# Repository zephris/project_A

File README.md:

# PHBox

RP2350A arcade controller: 13/16-button layout, Kailh Choc V2 switches, per-key RGB, SH1106 OLED, USB-C input and top-side USB-A host port. Uses configurable GP2040-CE pin assignments; hardware compatibility remains a prototype test.

**30 October ergonomic revision:** [higher/wider PCB and matching case candidate](mechanical/ergonomic_layout_2026-10-30/README.md), with 32 mm action-column spacing, 20 mm Choc V2-compatible SGF MonKeys/generic round caps and more palm space. The cap selection and cover-opening inputs are updated; current export status is recorded in the candidate README. Electrical routing remains unfinished. The root PCB and earlier mock-print packages retain the preceding layout.

The **[replacement-only A1 print job](mechanical/ergonomic_layout_2026-10-30/REPRINT_A1/README.md)** regenerates the changed mock parts plus three PLA blanking plugs as one supported vertical stack. It uses PLA models and PETG release interfaces; unchanged pieces of the earlier kit are reused.

## Active design and manufacture

- Active KiCad 10 sources: [project](Flatbox-rev8.kicad_pro), [schematic](Flatbox-rev8.kicad_sch), [PCB](Flatbox-rev8.kicad_pcb), plus local libraries and `3dmodels`.
- **USB2 moved to the top on 8 October:** [revision and checks](mechanical/USB2-top-assessment-2026-10-08.md). Existing manufacturing files below are the preceding bottom-side revision; regenerate Gerbers/CPL and visually approve USB2 orientation before ordering the current PCB.
- [Manufacturing package](manufacturing/PHBox_2026-10-06_DFM_resolved/README.md), [complete ZIP](manufacturing/PHBox_2026-10-06_DFM_resolved.zip), [mandatory notes](manufacturing/PHBox_2026-10-06_DFM_resolved/MANUFACTURING-NOTES.md) and [DFM evidence](manufacturing/PHBox_2026-10-06_DFM_resolved/validation/rerun-summary.md).
- C41 / C29936 is included in BOM/CPL. Refresh the separate BOM matching site and visually approve placements, especially USB2, before assembly release.
- **USB2 replaced on 9 October:** [C2344 through-hole revision and checks](mechanical/USB2-C2344-assessment-2026-10-09.md). Uses Jing 902-131A1021D10100, with a drawing-derived STEP seated at the PCB datum. Existing manufacturing exports and quote still need regeneration; request mixed-assembly solder-process review for this through-hole part.

## Ordering guide

Current quote selections read on 8 October 2026; no order submitted. These are selected form values, not factory acceptance.

| Option | Selected value |
|---|---|
| Base material / material grade | FR-4 / FR4 TG135 |
| Layers / product type | 4 / Industrial/Consumer electronics |
| Designs / delivery | 1 / Single PCB |
| PCB quantity | 5 |
| Thickness | 1.6 mm |
| Mask / silkscreen | Black / White |
| Surface finish | HASL (with lead) |
| Outer / inner copper | 1 oz / 0.5 oz |
| Specify layer sequence / stackup | Yes / Yes |
| Stackup | JLC04161H-7628 |
| Impedance control | No requirement |
| Via covering | Epoxy Filled & Capped (selected; control currently disabled) |
| Via plating | Horizontal Electroless Copper Plating |
| Minimum via hole/land | 0.3 mm / 0.4–0.45 mm |
| Outline tolerance | ±0.2 mm (Regular) |
| Confirm production files | Yes; automatic approval disabled in earlier verified dialog |
| Mark / electrical test | Remove Mark / Flying Probe Fully Test |
| Gold fingers / castellated holes | No / No |
| Press-fit holes / edge plating | No / No |
| Blind slots / backdrill | No / No |
| UL marking / humidity indicator card | No / No |
| PCBA type / assembly side | Standard / Both Sides |
| PCBA quantity | 5 |
| Edge rails/fiducials | Added by JLCPCB; two 5 mm rails |
| Confirm parts placement | Yes |
| Stencil storage / fixture storage | No / No |
| Parts selection | By Customer (Self-Service) |
| Separate stencil order | Not enabled; no separate stencil thickness selected |

The quote displays **272.6 × 181 mm including assembly rails**; finished board artwork is **272.65 × 171.05 mm**. Follow the Gerber outline and verify dimensions in production artwork; do not resize the PCB to the rail-inclusive size. A depaneling service is suggested by the page but its selection is not verified.

Upload the [Gerber-only ZIP](manufacturing/PHBox_2026-10-06_DFM_resolved/upload/PHBox-DFM-resolved-Gerbers.zip), then [BOM](manufacturing/PHBox_2026-10-06_DFM_resolved/assembly/BOM-JLCPCB.csv) and [CPL](manufacturing/PHBox_2026-10-06_DFM_resolved/assembly/CPL-JLCDFM.csv) separately. Refresh the separate BOM matching site and visual preview, including C41 and USB2.

### Additional requirements and remarks

The **PCB remark is currently empty** in the live form, despite earlier entry; re-enter before submission. The current page does not expose a PCBA remark field. The short text below is prepared for that field, not already entered.

- Obtain explicit CAM confirmation that all nine **U1 0.35 mm ComponentDrill thermal holes** receive epoxy filling and copper capping. Ordinary via selection alone is insufficient. Preserve other component holes and use the supplied U1 hole map.
- Preserve U4's six **0.664 × 0.190 mm** paste apertures; obtain complete-board approval of a **0.10 mm stencil**. These are additional instructions, not selected quote options. Confirm X-ray inspection of U1's hidden exposed-pad joint.
- Confirm hand/THT assembly, OLED support and socket procurement. Retain manufacturer-land-pattern dispositions for D21/U1/U4/F1; verify polarity and accepted CPL rotations.
- **Leaded HASL differs from the source's Lead-Free setting.** Resolve finish before submission. Impedance control is not selected; USB impedance remains an engineering check against the chosen stackup.

Short additional-order remark (181 characters):

> U1: fill/cap 9 thermal ComponentDrill holes; X-ray EP joint. U4: keep 6 paste apertures 0.664x0.190mm; review 0.10mm stencil. Confirm manual parts, polarity and CPL before assembly.

The complete [manufacturing notes](manufacturing/PHBox_2026-10-06_DFM_resolved/MANUFACTURING-NOTES.md) and [ordering review](manufacturing/ordering-review-2026-10-08.md) retain dimensions, hole locations and acceptance requirements that cannot fit into one 200-character field.

## Final assembly by the user

Use the [sectioned final-assembly BOM and Perth-first supplier list](mechanical/assembly_bom_2026-10-31/README.md)
for quantities, purchasing status and exact-size requirements. It covers one unit
with 16 Choc V2 switches, 13 fitted 20 mm caps and three PLA blanking plugs.
Custom PETG keycaps are an authorized fallback if exact purchased caps cannot be
obtained with practical delivery; no new keycap model is included in the BOM.

Use the [current wider-layout part files](mechanical/ergonomic_layout_2026-10-30/README.md)
with the [17 mm sandwich assembly sequence](mechanical/sandwich_17mm_2026-10-08/README.md).
The wider PCB still requires routing and fresh manufacturing exports. Its combined
assembly STEP contains the earlier top cover; use the individual current parts.
This is a **prototype assembly guide**: nominal CAD fits have passed, but real
switches, hardware, foam and thermal pads must be trial-fitted before making the
finished enclosure. Overall case size is **292.6 × 191 × 17 mm**, excluding keycaps.

### How the parts are mounted

The layer order is **top acrylic → upper spacer and internal parts → PCB → foam
→ lower spacer/carrier → bottom acrylic**. The upper and lower spacer walls close
the perimeter; their heights are already included in the 17 mm total.

| Assembly | Mounting solution |
|---|---|
| Acrylic covers and spacer walls | Eight rigid columns outside the PCB: 12 mm M3 female/female spacers, with a 0.50 mm washer at each end. Screws enter from both covers. |
| PCB | Seven relieved foam pads beneath it; six upper foam pads capture the switch-plate tabs. Loose guides at H4/H6 locate it laterally. No case screws clamp through the PCB. |
| Choc V2 switch plate | Three custom insulating post/retainer pairs at H1/H2/H3, with polymer M3 screws. The 1.30 mm plate sits 3 mm above the PCB seating plane. |
| MCU/flash heatsink | Insulating hard stops, support washers and rear retainers at H5/H7/H12. Separate thermal pads contact U1 and U3. This attaches to the PCB, not the case. |
| OLED | Four custom insulating posts and rear caps, plus a corner frame and polymer M2 screws. The frame retains the module PCB without pressing its glass. |
| Option-button caps | Six captured plungers guided by the acrylic and a lower retainer. Two M2 screws secure the retainer to the cover; switch contact domes provide click and return. |
| USB ports | Integral spacer surrounds and compliant collars. Acrylic roofs USB-A; the spacer roofs USB-C. The collars close shell gaps while allowing PCB movement. |

The PCB, switch plate, heatsink and screen move together as one foam-supported
assembly. The CAD budgets ±0.50 mm XY and ±0.25 mm Z movement. Do not turn the
port collars, button guides or mounting screws into rigid links between it and
the outer case.

### Parts to prepare

| Part | Quantity / specification |
|---|---|
| Acrylic covers / printed spacer frames | One top and one bottom of each; acrylic is 2 mm thick |
| Case columns / end washers | 8 × M3 female/female, 12 mm, AF5; 16 × Ø7 / Ø3.4 / 0.50 mm washers |
| Case screws | 16 × M3×6, 90° countersunk |
| Switch-plate mounts / screws | 3 custom insulating post/cap pairs; 3 × M3×8 polymer, head no larger than Ø6 × 2.4 mm |
| OLED mounts / screws | 4 custom insulating post/cap pairs; 4 × M2×8 polymer, head no larger than Ø4 × 1.6 mm |
| Heatsink mounting set | 3 insulating hard stops, 3 support washers, 3 relieved rear washers and 3 tapped rear retainers; polymer M3 at H5/H7 and M2 at H12. Select screw lengths after measuring the assembled stack. |
| Thermal pads | Two electrically insulating pads: MCU 5.5 × 5.5 mm; flash 3.5 × 3.5 mm. Starting assumption: 0.50 mm free / 0.40 mm installed thickness. |
| Support foam | 7 lower pads from 2 mm stock; 6 upper pads from 1.5 mm stock, using the supplied cut profiles |
| Port collars | 2 printed unfilled, nonconductive TPU 95A trial collars, 2 mm deep; separate front-face-down STLs include the rear PCB rebates |
| Option caps / retainer / fasteners | 6 caps, 1 retainer, 2 × M2×5 pan-head screws (head ≤ Ø4 × 1.6 mm), 2 × M2 nuts (AF4 × 1.6 mm) |

Custom insulating mounts and retainers are supplied CAD parts, not ordinary
catalog standoffs. The heatsink uses flat insulating support washers in the
current model; an O-ring is an alternative only after checking its compressed
height and force. Keep the hard stops with either choice. Exact foam and thermal-pad
grades, heatsink screw lengths and the option-switch MPN remain to be qualified.

### TPU USB collars

Print one each of [USB-A](mechanical/sandwich_17mm_2026-10-08/STL/usb_a_collar.stl) and
[USB-C](mechanical/sandwich_17mm_2026-10-08/STL/usb_c_collar.stl). Both files are oriented
front mating face down on Z=0, with the rear PCB relief upward. Use unfilled,
nonconductive TPU 95A as the economical first trial. The PCB supports remain cut
foam and the other mounts keep their existing materials.

Start with 0.10 mm layers, dried filament and the filament maker's temperature
profile. Inspect the sliced rear relief: it leaves a **0.317 mm front membrane**.
Check that it prints continuously without tears; do not thicken it into the PCB
clearance. The supplied orientation avoids a roof over the rear relief. Trial
both collars before printing the full case, checking insertion, unplugging,
retention and freedom of the foam-mounted PCB. The intentional interference is
0.20 mm at the outer surround and 0.10 mm at the nominal connector shell.

Saved geometry clears the PCB travel envelope; TPU stiffness, creep and retention
have not been physically qualified. The collars close gaps but have no ingress
rating. Ordinary TPU does not replace the electrically insulating thermal pads.
[Prusa flexible-filament guidance](https://help.prusa3d.com/article/flexible-materials_2057)
explains printing and drying considerations.

### Buying materials: cost and delivery priority

For an unpowered fit trial, use the [printed mock-kit guide](mechanical/sandwich_17mm_2026-10-08/MOCK_ONLY/README.md): individual STLs include acrylic surrogates, case columns, mounting parts, collars and simplified PCB/display envelopes. Large parts have quarter-panel alternatives. Plastic heatsink and rigid pad gauges are for geometry checks only; do not power the board with them fitted.

The **[35-step illustrated mock assembly manual](mechanical/sandwich_17mm_2026-10-08/MOCK_ONLY/output/pdf/PHBox_mock_assembly_manual.pdf)** shows one operation per page, quantities, movement arrows, underside details and fit checks. Its [linked text version](mechanical/sandwich_17mm_2026-10-08/MOCK_ONLY/ASSEMBLY_STEPS.md) identifies every STL file used.

The [Bambu A1 PLA print package](mechanical/sandwich_17mm_2026-10-08/MOCK_ONLY/PRINT_A1/README.md) contains one part per 3MF project and validated slice for 0.6/0.4/0.2 mm nozzles. Six oversized parts are split into four sections each. The required kit has 86 individual files, about 471 g / 26.6 hours when printed separately; 19 optional gauge/envelope files are also supplied. Use one AMS Lite PLA colour per print; these estimates exclude nozzle changes, handling and physical fit qualification.

For the requested **single vertically stacked job**, use the [A1 PLA/PETG stack guide](mechanical/sandwich_17mm_2026-10-08/MOCK_ONLY/STACK_A1/README.md). All 105 parts retain their geometry inside an editable multipart assembly. Independently rising panel columns and low side pockets reduce support; 1 mm supported separators use PETG on both contact faces and PLA scaffold inside. The guide includes the small separation trial, full project/slice, actual estimates, numbered views and assembly-review limitations. Print the trial before the full stack.

The [31 October assembly BOM](mechanical/assembly_bom_2026-10-31/README.md)
supersedes the older AliExpress-first sourcing preference. Prioritise **Perth
pickup**, then Australian shipped exact parts, and international suppliers where
no exact local match is verified. It lists local thermal pads, hardware inquiries,
foam, acrylic cutting and aluminium machining. Exact store stock, fastener head
dimensions and custom quotes still need confirmation where marked. No purchases
or supplier inquiries have been made. The older
[materials list](mechanical/sandwich_17mm_2026-10-08/materials.md) remains a dated reference.

The [heatsink hardware audit and mounting alternatives](mechanical/sandwich_17mm_2026-10-08/heatsink-hardware-options.md)
lists concrete nylon screw/nut and case-column sources. Current heatsink rear
retainers provide only 2 mm nominal thread depth; screw length and engagement
remain unresolved. A PETG shoulder stop with stock nylon nuts in redesigned
capture carriers is the preferred prototype direction, subject to fit and
thermal/preload trials. TPU should not replace the height-setting hard stops.

### Assembly sequence

**Read the graphic from I upward:** build the lower case (I/H), add support foam (G), lower the assembled PCB and its attachments (F/E/D), then add the upper foam, spacer and prepared cover (C/B/A). Letters identify parts; the numbered steps below give the working sequence. Exploded gaps are illustrative, not installed heights.

The sections explain which parts clamp together and which must remain free to move. They are not machining drawings; use the hardware table and supplied STEP parts for dimensions. Full-resolution images are available by opening each graphic.

1. **Prepare and dry-fit the parts.** Deburr acrylic and aluminium, clean the
   printed guides and trial a real Choc V2 switch in the plate coupon. Check the
   actual PCB thickness, OLED tails, fastener heads and option-switch height.
   Acrylic case holes require the specified secondary 90° countersinks; support
   them during machining and trial a coupon before cutting the full covers.
2. **Build the PCB assembly.** Fit the OLED posts, module, corner frame and rear
   caps using the four polymer M2 screws. Attach the switch plate at H1/H2/H3
   using its three insulating mounts and polymer M3 screws. Fit the switches and
   confirm latching. Keep screw and frame loads off the OLED glass.
3. **Fit the heatsink.** Measure U1/U3 package heights and select the thermal-pad
   grade before setting contact gaps. Centre the two small pads on the package
   bodies, clear of leads and nearby components. Fit the insulating stops,
   washers and rear retainers at H5/H7/H12. Tighten only to the hard stops;
   inspect pad compression and PCB bending. BOOTSEL/RESET remain clear of the
   aluminium and are serviced by removing the top cover.
4. **Build the lower case.** Fit the eight columns, lower end washers and lower
   frame to the bottom acrylic with eight case screws. Place the seven lower
   foam pads in their relieved seats. Keep foam off sockets, solder tails and
   rear components. Lower the PCB assembly over the loose H4/H6 guides.
5. **Prepare the top cover.** Insert the six option caps from below, with their
   retaining flanges beneath the acrylic. Fit the lower retainer, captive nuts
   and two M2×5 screws. Check that each cap slides freely. No extra coil springs
   are required in this candidate.
6. **Fit the surrounds and close the case.** Place the six upper foam pads on
   the switch-plate capture tabs. Fit the upper spacer and the two port collars,
   including their printed rear PCB rebates. Trial the outer interference fit;
   if collars walk out, qualify thin TPU-compatible perimeter adhesive
   against their spacer seats; keep adhesive off the moving PCB and connector
   contacts. Add the upper end washers and top acrylic, then the remaining eight
   case screws. Tighten gently and evenly onto the fixed columns. Tune foam to
   achieve the PCB's rest height; do not pull the PCB down with case screw torque.
7. **Check mechanical operation before powering.** Every option cap must return
   and release its switch at both PCB travel extremes. Test full keycap stroke,
   screen retention and real USB cable/dongle insertion and removal. The USB-A
   fit gauge assumes a 2 mm setback between the mating face and dongle body;
   confirm this on the intended dongle. Check that the covers and foam do not
   contact rear tails or load the connector shells.
8. **Run the first-article checks.** Confirm all inputs, OLED, RGB and USB operation,
   then check MCU/flash temperatures in the closed case. Recheck cap return,
   foam rest height and fastener seating after initial use.

Use the [exploded STEP](mechanical/sandwich_17mm_2026-10-08/STEP/exploded.step)
to identify parts; its layer offsets are for presentation, not spacer dimensions.
The [detailed mechanical guide](mechanical/sandwich_17mm_2026-10-08/README.md)
contains cutting, countersink, clearance and fit-test specifications.

## Simulation and mechanics

- [17 mm foam sandwich mounting candidate](mechanical/sandwich_17mm_2026-10-08/README.md): acrylic covers, spacers/carrier, Choc V2 plate, screen frame/posts and integrated PCB/heatsink assembly. USB-A pocket ends at the main case edge, with a 2 mm acrylic USB-A roof, lower printed USB-C roof and integral soft-seal retaining lips at 17 mm overall; plan size 292.6 × 191 mm. Six captured option caps replace the exposed button slot. Fit candidate; actual switches, foam preload, seals and hardware tolerances need trials.
- [Mounting and Perth hardware sourcing](mechanical/mounting_sourcing_2026-10-08.md): gasket-supported PCB/heatsink/screen carrier, local fasteners and thermal-pad candidates; custom insulating stops remain necessary. [Choc V2 LED-window fit study](mechanical/choc_v2_led_fit_2026-10-08/README.md) contains fit/section STEP models and all-key clearance checks.
- [MCU/flash aluminium heatsink candidate](mechanical/heatsink_2026-10-08/README.md): milled plate, separate insulating thermal pads, BOOTSEL/RESET access and checked board fit. Contact heights and pad force still require assembled-hardware qualification.
- [SPICE suite](spice/README.md): 14 isolated benches; [latest results](spice/results_static_retest_2026-10-07.md). First articles still need power, USB suspend, firmware, thermal and dongle tests.
- [Enclosure principles](mechanical/enclosure_2026-10-05/DESIGN-PRINCIPLES.md), [candidates](mechanical/enclosure_2026-10-05/README.md), [PCB tolerances](mechanical/enclosure_2026-10-05/pcb_geometry/README.md) and [Z geometry](mechanical/enclosure_2026-10-05/z_geometry/index.html). Choc V1 plate references need V2 fit verification.
- USB2: Jing 902-131A1021D10100 / C2344, through-hole on the top side beside USB-C; [current assessment](mechanical/USB2-C2344-assessment-2026-10-09.md). The [sandwich candidate](mechanical/sandwich_17mm_2026-10-08/README.md) has a flat 17 mm case with an acrylic connector roof and open-top dongle pocket (2 mm dongle body setback requires a physical check); older 26 mm covers remain historical references. A 15 mm version needs further height changes.

`stage2_work` retains active parsers, production-silk generation and CAD dependencies; `kicad-happy-main` contains project skills. [Cleanup manifest](manufacturing/cleanup-manifest-2026-10-07.json).

The latest [reference-case study](mechanical/sandwich_17mm_2026-10-08/reference-case-study.md)
records the contoured USB surrounds, foam-motion clearances and option-button
comparison. USB-A is acrylic-roofed; USB-C is spacer-roofed. Captured H5 option
plungers rely on the tact switches for click/return, without auxiliary springs.

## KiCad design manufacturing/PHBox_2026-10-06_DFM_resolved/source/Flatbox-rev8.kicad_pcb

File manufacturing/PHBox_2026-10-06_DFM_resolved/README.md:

# Current PHBox demo fabrication and assembly package

The latest package includes C41 Samsung CL10B105KA8NNNC / C29936, 1uF/25V/X7R, at its existing bottom-side origin and zero rotation. BOM/CPL contain the same 112 designators in 36 BOM groups. Source metadata is updated; fabrication copper, drill, stencil and production silk files are unchanged. This metadata-only addition does not invalidate the saved PCB geometry review; refreshed online BOM matching/assembly preview remains required.

Use upload/PHBox-DFM-resolved-Gerbers.zip for PCB upload, assembly/BOM-JLCPCB.csv and assembly/CPL-JLCDFM.csv on the separate BOM matching page, and both stencil paste files with the assembler. The complete distributable is ../PHBox_2026-10-06_DFM_resolved.zip.

MANUFACTURING-NOTES.md is authoritative. The obsolete assembly-note.txt was removed. JLCPCB CAM must still confirm all nine U1 ComponentDrill thermal holes receive epoxy filling and copper capping. Obtain complete stencil approval, actual-package disposition and final production artwork review before ordering. Source silk is restored; use the supplied clearance-clipped production silk exports.

Saved final geometry analysis: validation/rerun-summary.md and findings-disposition.md. Website candidate 630408027919675394 predates adding C41 to assembly files. No online placement confirmation of C41 is claimed. Bare PCBA is an engineering prototype, with hardware/power/thermal qualification pending. Hot-swap sockets and mechanical support need an explicit assembly/procurement arrangement.

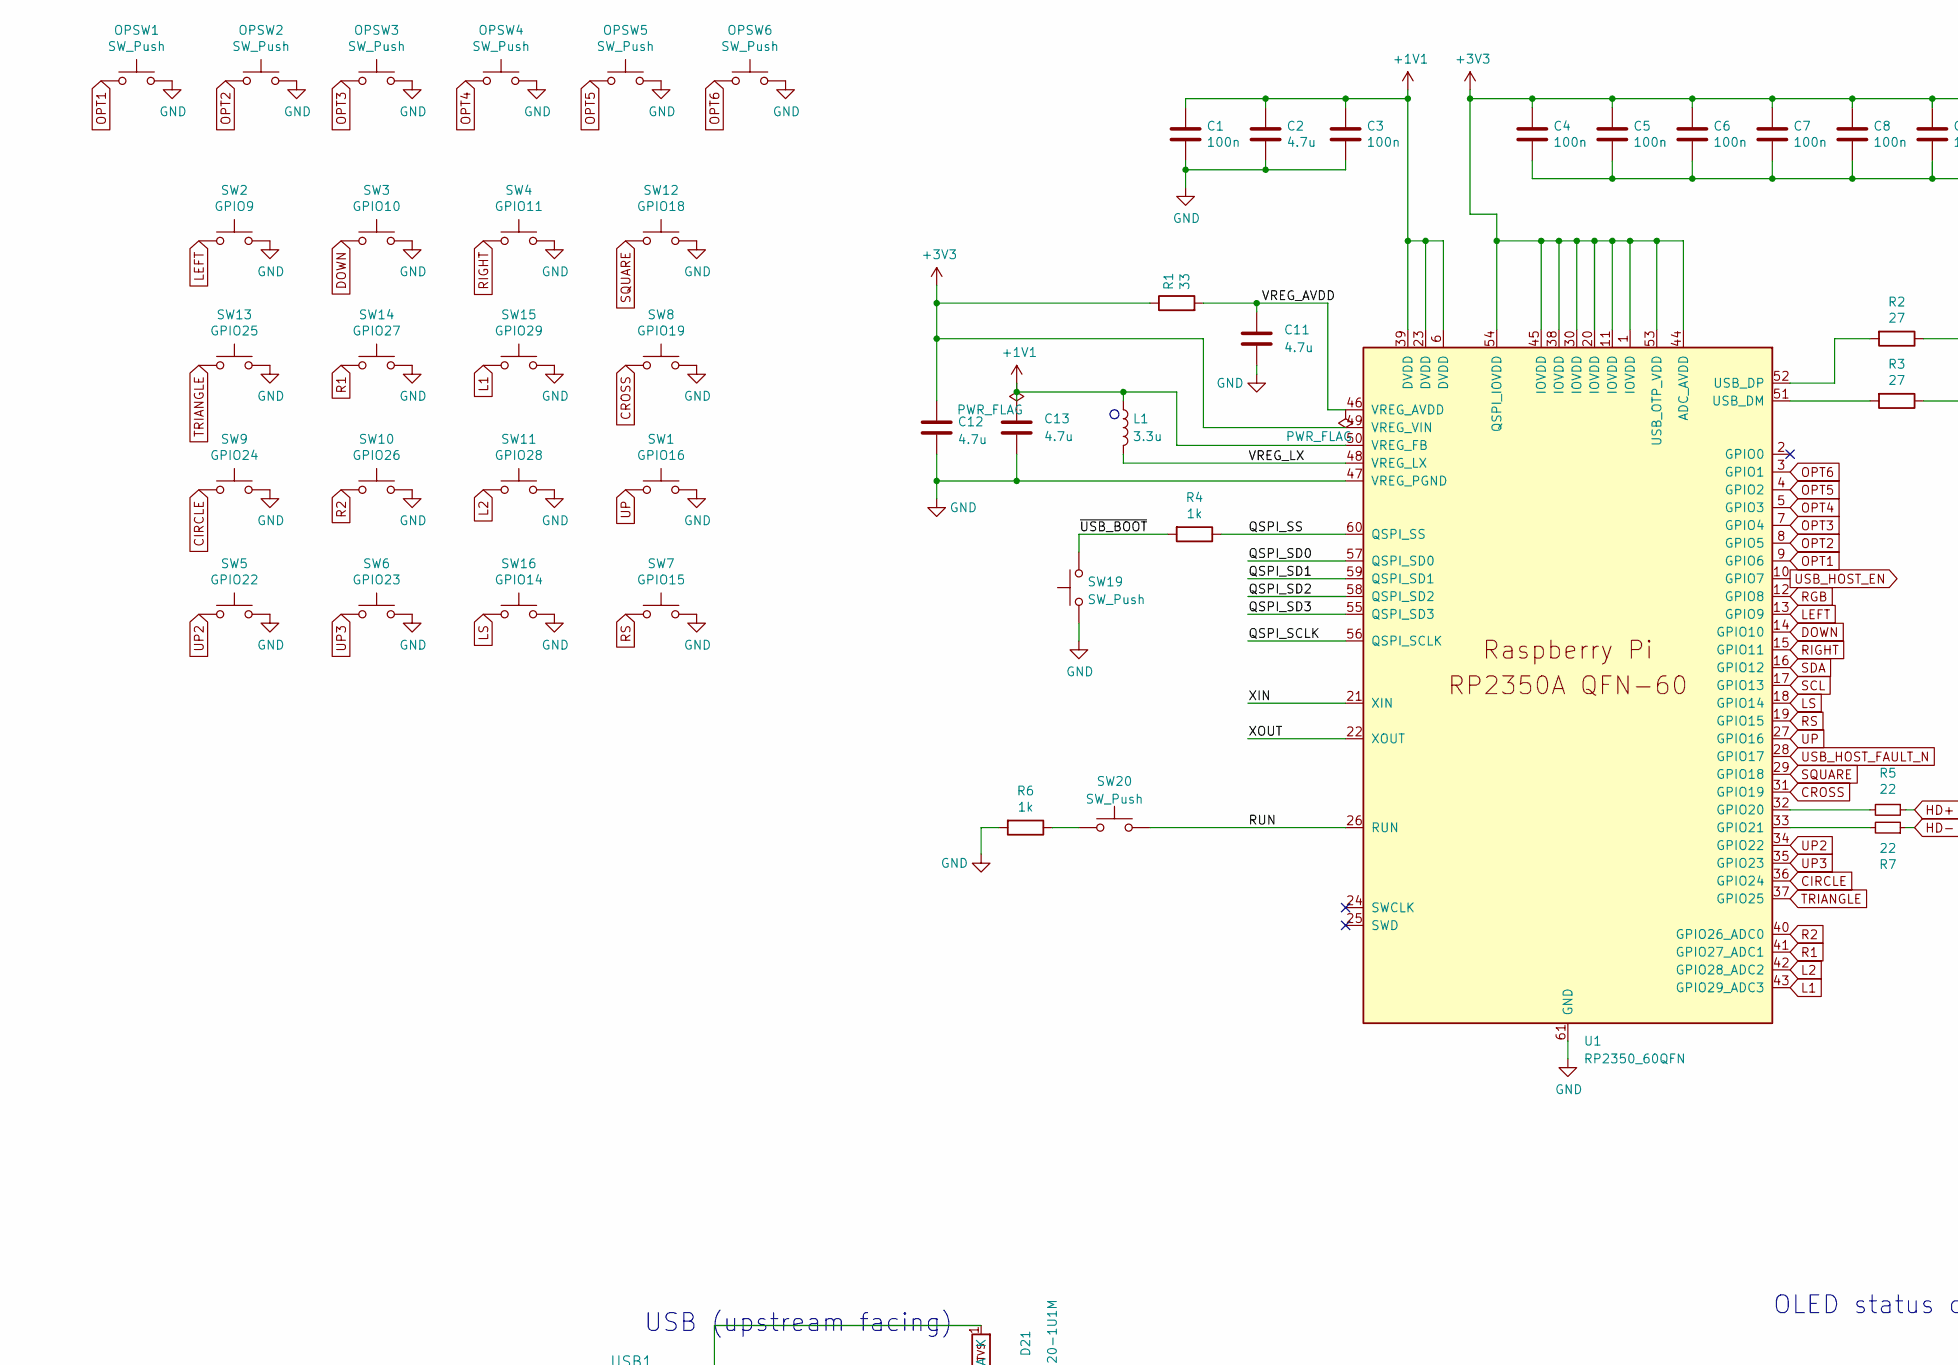
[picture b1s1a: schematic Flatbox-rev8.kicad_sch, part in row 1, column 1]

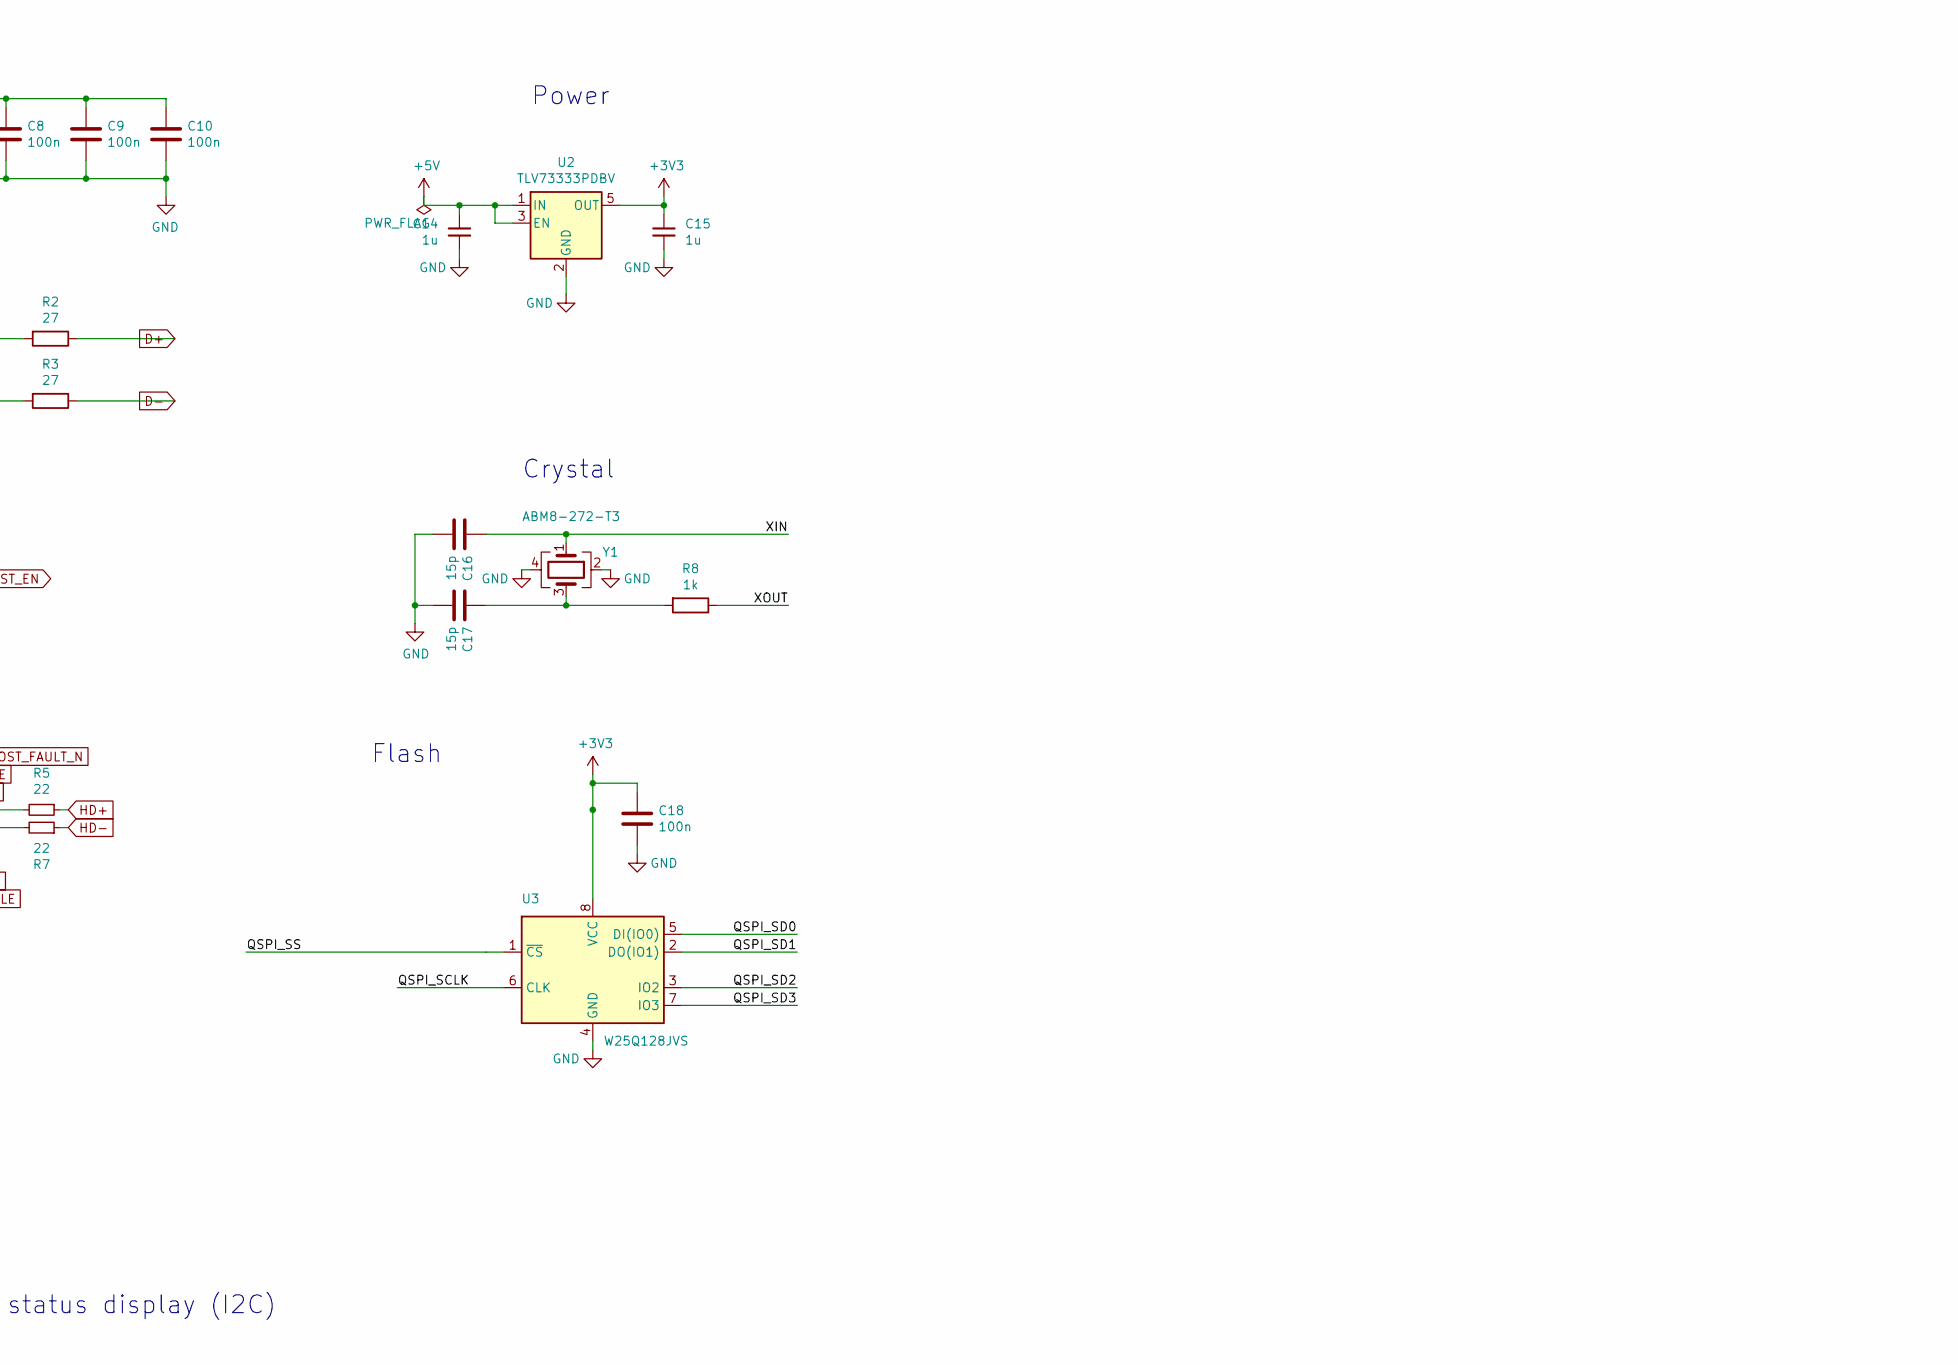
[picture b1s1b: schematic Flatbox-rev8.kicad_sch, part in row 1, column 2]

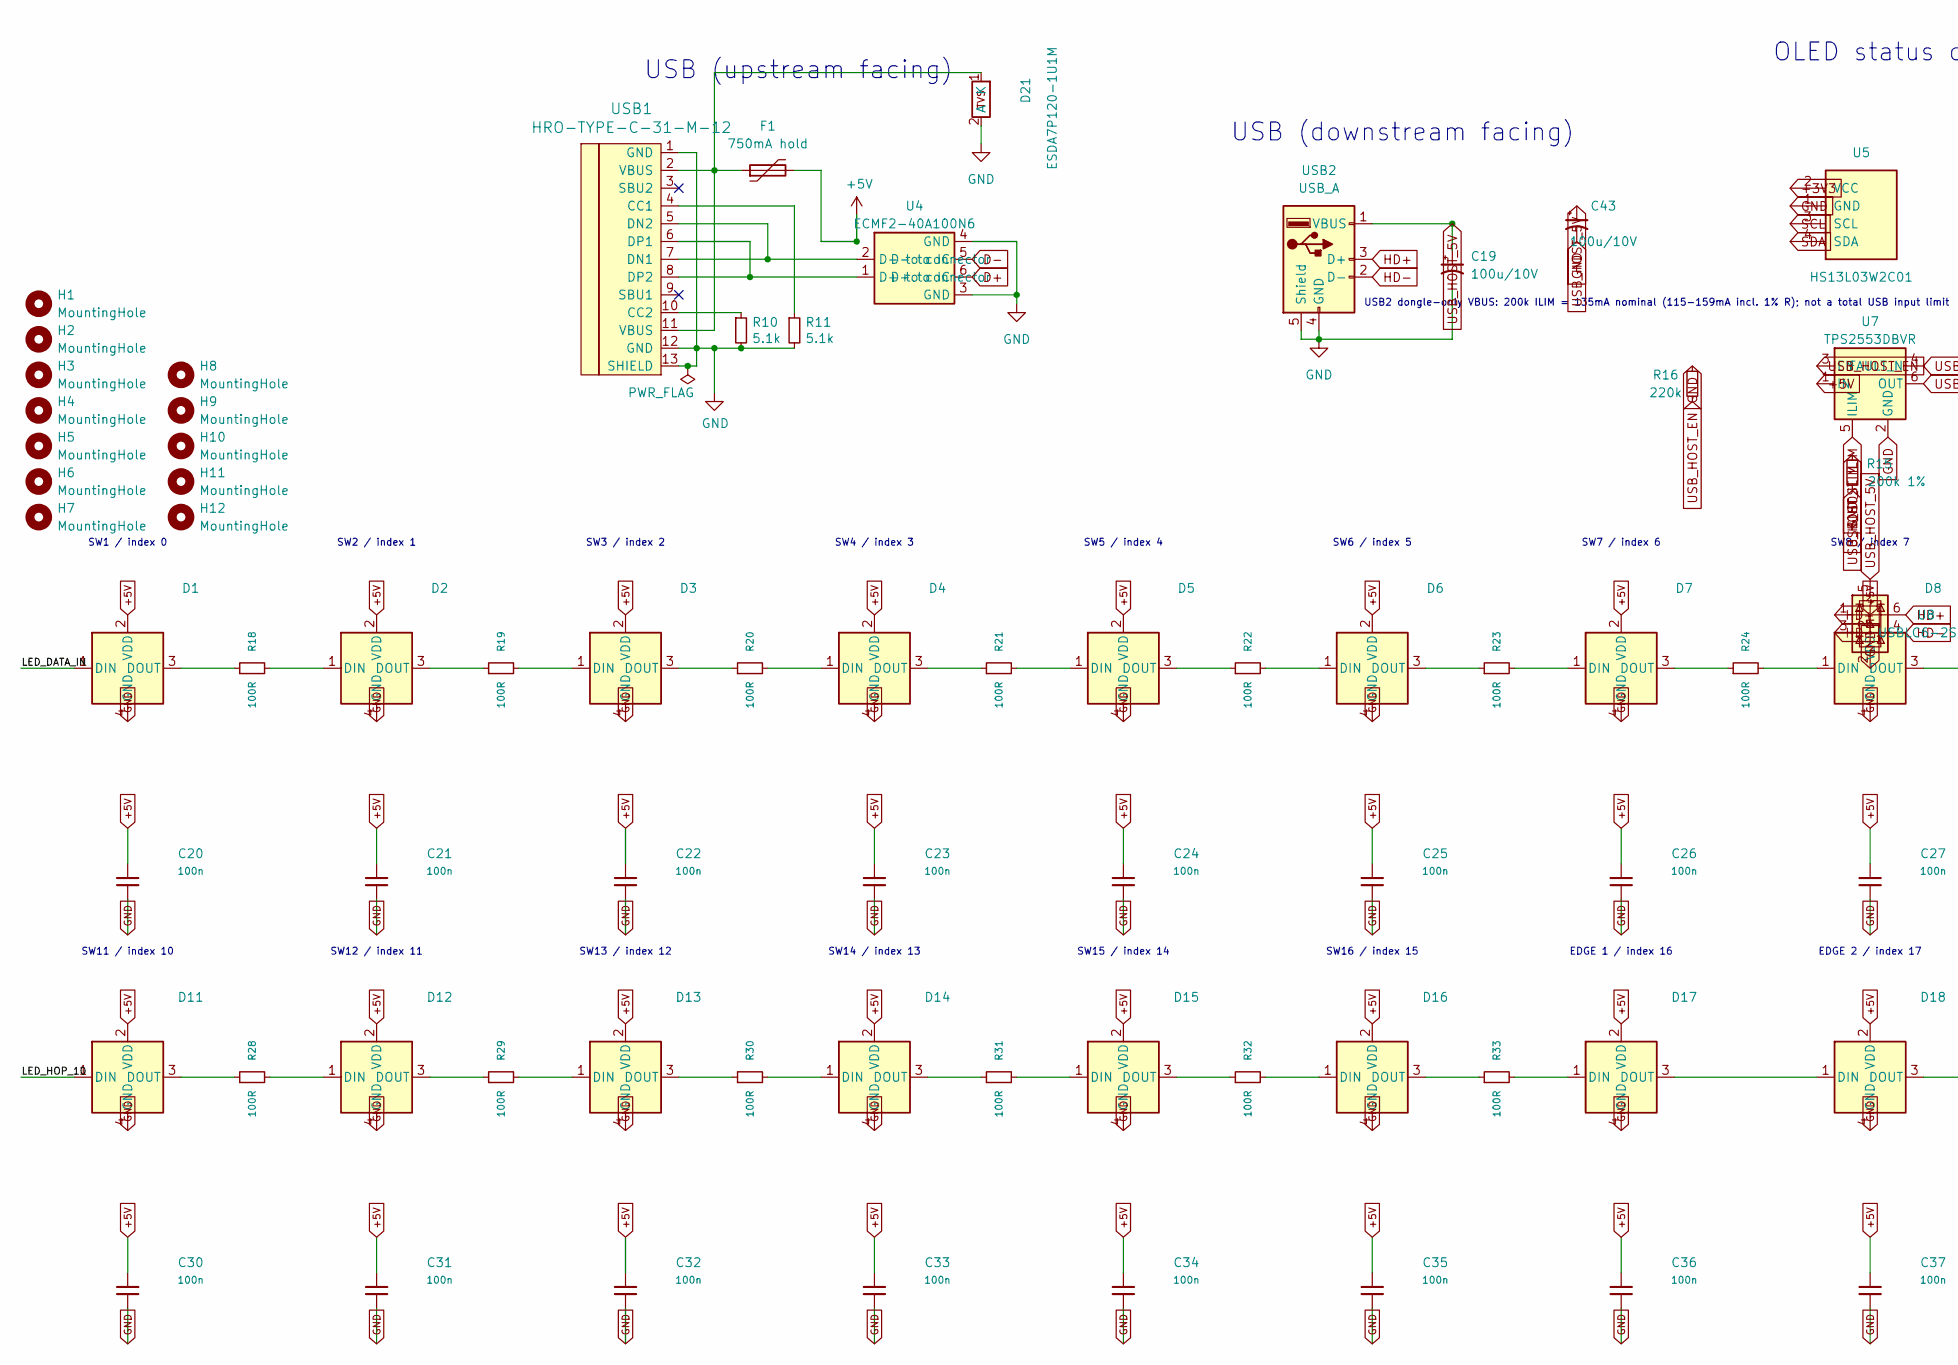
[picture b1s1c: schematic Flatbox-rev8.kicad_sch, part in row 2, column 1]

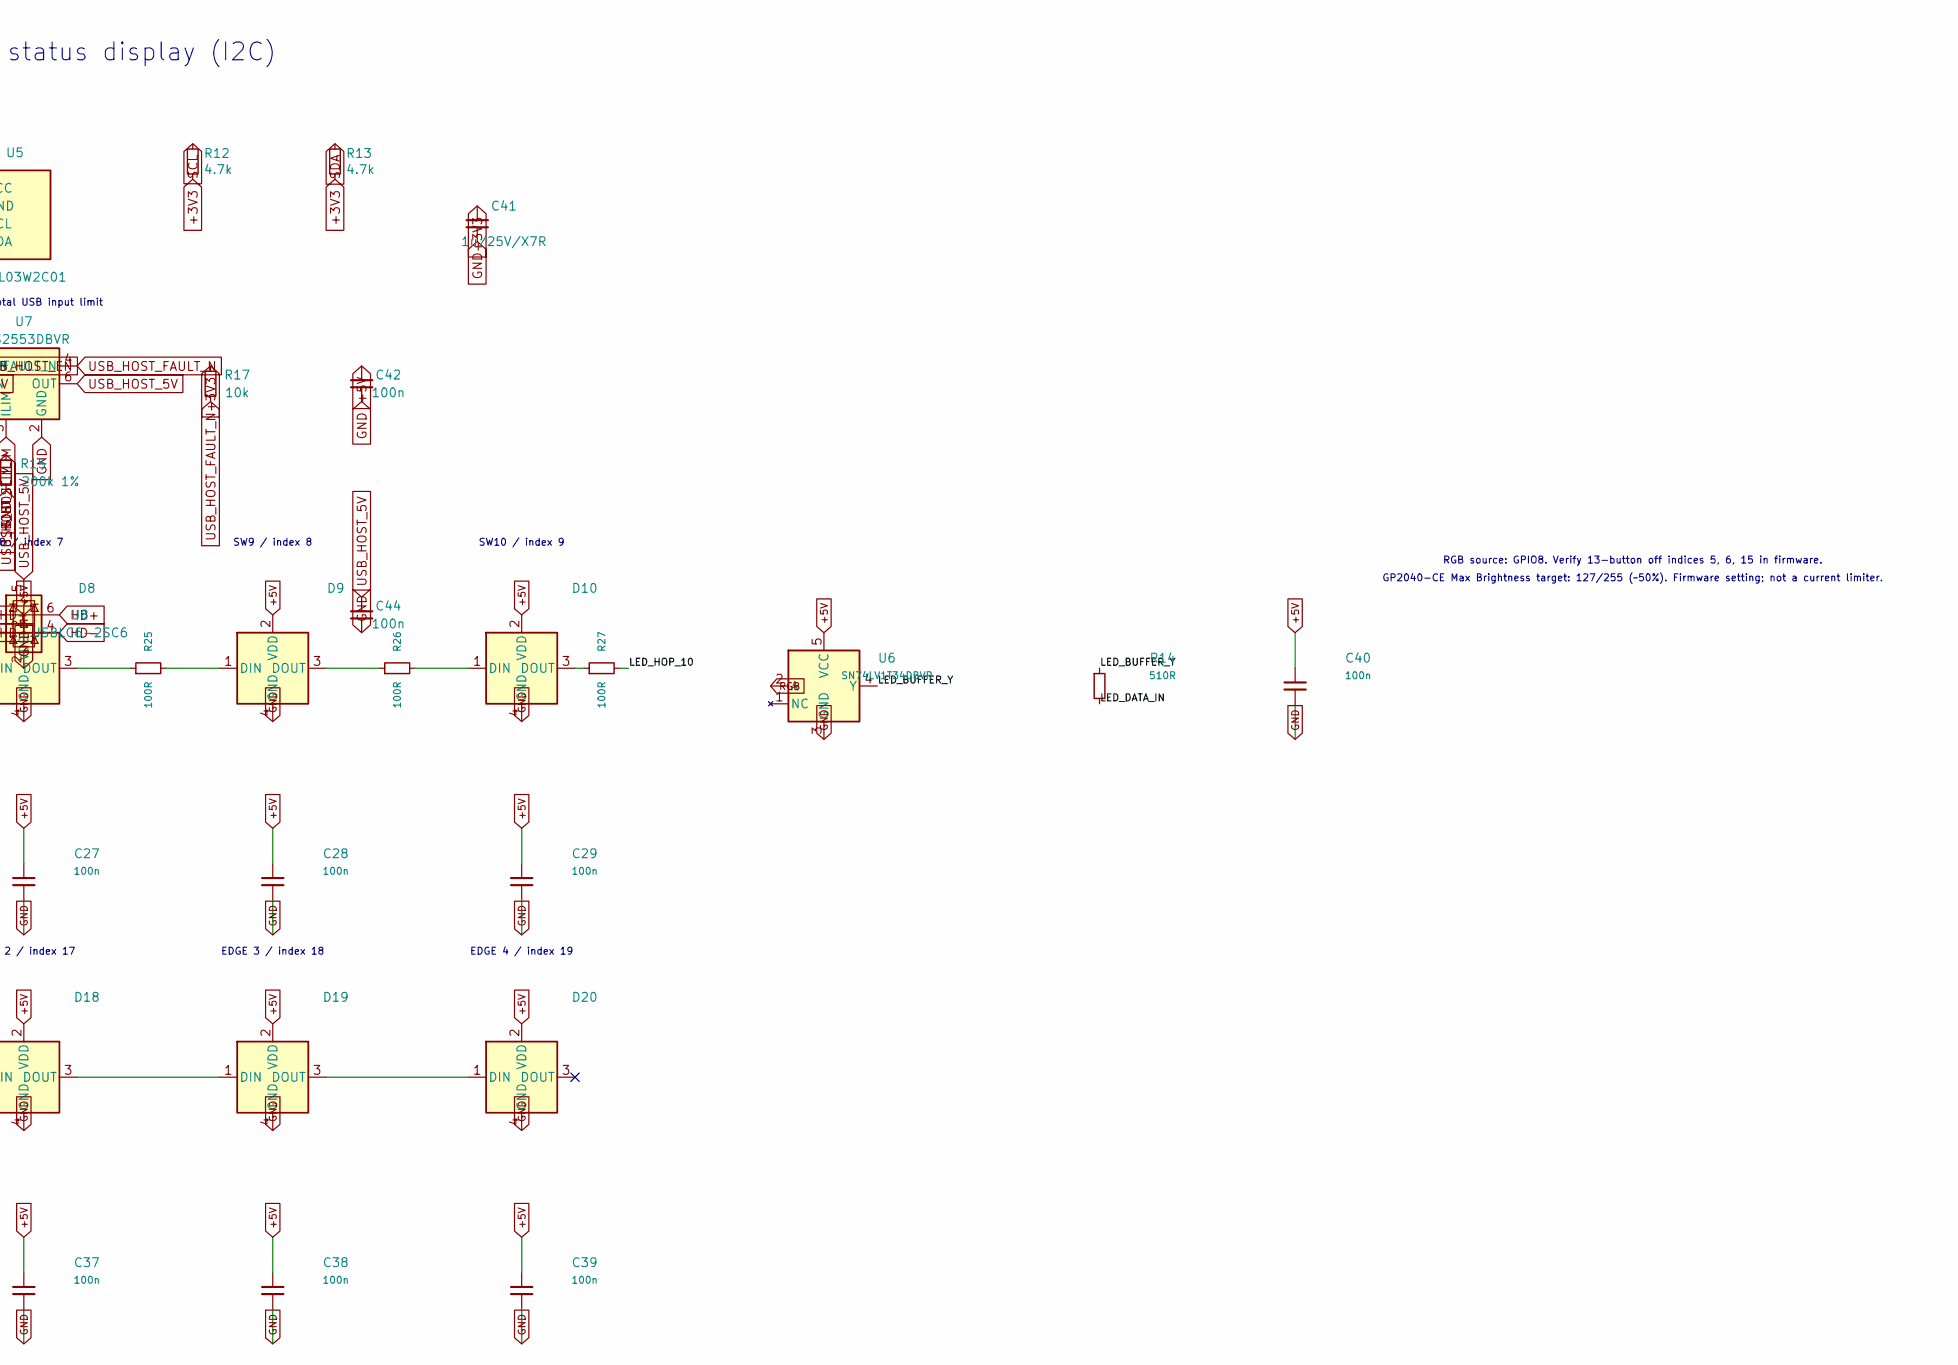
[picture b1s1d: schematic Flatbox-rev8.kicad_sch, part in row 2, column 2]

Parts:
C1, C3, C4, C5, C6, C7, C8, C9, C10, C18: 100n; C_0402_1005Metric; LCSC C1525
C2, C11: 4.7u; C_0402_1005Metric; LCSC C23733
C12, C13: 4.7u; Samsung_1005_Tolerance015; LCSC C23733
C14, C15: 1u; C_0402_1005Metric; LCSC C52923
C16, C17: 15p; C_0402_1005Metric; LCSC C1548
C19, C43: 100u/10V; CP_KEMET_T520B_3528_21; MPN T520B107M010ATE070; LCSC C600583
C20, C21, C22, C23, C24, C25, C26, C27, C28, C29, C30, C31, C32, C33, C34, C35, C36, C37, C38, C39, C40: 100n; Samsung_1005_Tolerance005; MPN CL05B104KO5NNNC; LCSC C1525
C41: 1u/25V/X7R; C_0603_1608Metric; MPN CL10B105KA8NNNC; LCSC C29936
C42, C44: 100n; C_0402_1005Metric; MPN CL05B104KO5NNNC; LCSC C1525
D1, D2, D3, D4, D5, D6, D7, D8, D9, D10, D11, D12, D13, D14, D15, D16, D17, D18, D19, D20: SK6805-EC15; LED_SK6805_EC15_Optical; MPN SK6805-EC15; LCSC C2890035
D21: ESDA7P120-1U1M; ESDA7P120_1U1M_ST_Recommended; MPN ESDA7P120-1U1M; LCSC C2969802
F1: 750mA hold; Fuse_TECHFUSE_SMD0805_075_12V; MPN SMD0805-075-12V; LCSC C19108399
H1, H2, H3, H4, H5, H6, H7: MountingHole; MountingHole_6.4mm_M6
H8, H9, H10, H11, H12: MountingHole; MountingHole_2.2mm_M2
L1: 3.3u; L_pol_2016; LCSC C42411119
OPSW1, OPSW2, OPSW3, OPSW4, OPSW5, OPSW6: SW_Push; SW_PUSH_6mm_H5mm
R1: 33; R_0402_1005Metric; LCSC C25105
R2, R3: 27; R_0402_1005Metric; LCSC C138021
R4, R6, R8: 1k; R_0402_1005Metric; LCSC C11702
R5, R7: 22; R_0402_1005Metric; LCSC C102906
R10, R11: 5.1k; R_0402_1005Metric; LCSC C25905
R12, R13: 4.7k; R_0603_Compact; MPN 0603WAF4701T5E; LCSC C23162
R14: 510R; R_0402_1005Metric; MPN 0402WGF5100TCE; LCSC C25123
R15: 200k 1%; R_0402_1005Metric; MPN 0402WGF2003TCE; LCSC C25764
R16: 220k; R_0402_1005Metric; MPN 0402WGF2203TCE; LCSC C25767
R17: 10k; R_0402_1005Metric; MPN 0402WGF1002TCE; LCSC C25744
R18, R19, R20, R21, R22, R23, R24, R25, R26, R27, R28, R29, R30, R31, R32, R33: 100R; R_0402_1005Metric; MPN 0402WGF1000TCE; LCSC C25076
SW1: GPIO16; SW_Hotswap_Kailh_Choc_V1V2_3D_Optical
SW2: GPIO9; SW_Hotswap_Kailh_Choc_V1V2_3D_Optical
SW3: GPIO10; SW_Hotswap_Kailh_Choc_V1V2_3D_Optical
SW4: GPIO11; SW_Hotswap_Kailh_Choc_V1V2_3D_Optical
SW5: GPIO22; SW_Hotswap_Kailh_Choc_V1V2_3D_Optical
SW6: GPIO23; SW_Hotswap_Kailh_Choc_V1V2_3D_Optical
SW7: GPIO15; SW_Hotswap_Kailh_Choc_V1V2_3D_Optical
SW8: GPIO19; SW_Hotswap_Kailh_Choc_V1V2_3D_Optical
SW9: GPIO24; SW_Hotswap_Kailh_Choc_V1V2_3D_Optical
SW10: GPIO26; SW_Hotswap_Kailh_Choc_V1V2_3D_Optical
SW11: GPIO28; SW_Hotswap_Kailh_Choc_V1V2_3D_Optical
SW12: GPIO18; SW_Hotswap_Kailh_Choc_V1V2_3D_Optical
SW13: GPIO25; SW_Hotswap_Kailh_Choc_V1V2_3D_Optical
SW14: GPIO27; SW_Hotswap_Kailh_Choc_V1V2_3D_Optical
SW15: GPIO29; SW_Hotswap_Kailh_Choc_V1V2_3D_Optical
SW16: GPIO14; SW_Hotswap_Kailh_Choc_V1V2_3D_Optical
SW19, SW20: SW_Push; SW_C318884_FabOnly; LCSC C318884
U1: RP2350_60QFN; RP2350-QFN-60-1EP_7x7_P0.4mm_EP3.4x3.4mm_ThermalVias; LCSC C42411118
U2: TLV73333PDBV; SOT-23-5; LCSC C134139
U3: W25Q128JVS; SOIC-8_5.23x5.23mm_P1.27mm; LCSC C97521
U4: ECMF2-40A100N6; MPN ECMF2-40A100N6; LCSC C5267592
U5: HS13L03W2C01; OLED_HS13L03W2C01; MPN HS13L03W2C01; LCSC C7465997
U6: SN74LV1T34DBVR; SOT-23-5; MPN SN74LV1T34DBVR; LCSC C100024
U7: TPS2553DBVR; SOT-23-6; MPN TPS2553DBVR; LCSC C55266
U8: USBLC6-2SC6; SOT-23-6; MPN USBLC6-2SC6; LCSC C7519
USB1: HRO-TYPE-C-31-M-12; HRO-TYPE-C-31-M-12-Assembly; LCSC C165948
USB2: USB_A; USB_A_904-131A2032S10200; MPN 904-131A2032S10200; LCSC C46400
Y1: ABM8-272-T3; Crystal_SMD_3225-4Pin_3.2x2.5mm; LCSC C20625731

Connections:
+1V1: C1.1, C2.1, C3.1, C13.1, L1.1, U1.6 (DVDD), U1.23 (DVDD), U1.39 (DVDD), U1.50 (VREG_FB)
+3V3: C4.1, C5.1, C6.1, C7.1, C8.1, C9.1, C10.1, C12.1, C15.1, C18.1, C41.1, R1.1, R12.2, R13.2, R17.1, U1.1 (IOVDD), U1.11 (IOVDD), U1.20 (IOVDD), U1.30 (IOVDD), U1.38 (IOVDD), U1.44 (ADC_AVDD), U1.45 (IOVDD), U1.49 (VREG_VIN), U1.53 (USB_OTP_VDD), U1.54 (QSPI_IOVDD), U2.5 (OUT), U3.8 (VCC), U5.2 (VCC)
+5V: C14.1, C20.1, C21.1, C22.1, C23.1, C24.1, C25.1, C26.1, C27.1, C28.1, C29.1, C30.1, C31.1, C32.1, C33.1, C34.1, C35.1, C36.1, C37.1, C38.1, C39.1, C40.1, C42.1, D1.2 (VDD), D2.2 (VDD), D3.2 (VDD), D4.2 (VDD), D5.2 (VDD), D6.2 (VDD), D7.2 (VDD), D8.2 (VDD), D9.2 (VDD), D10.2 (VDD), D11.2 (VDD), D12.2 (VDD), D13.2 (VDD), D14.2 (VDD), D15.2 (VDD), D16.2 (VDD), D17.2 (VDD), D18.2 (VDD), D19.2 (VDD), D20.2 (VDD), F1.2, U2.1 (IN), U2.3 (EN), U6.5 (VCC), U7.1 (IN)
/LED_BUFFER_Y: R14.1, U6.4 (Y)
/LED_DATA_IN: D1.1 (DIN), R14.2
/LED_HOP_10: D11.1 (DIN), R27.2
/QSPI_SCLK: U1.56 (QSPI_SCLK), U3.6 (CLK)
/QSPI_SD0: U1.57 (QSPI_SD0), U3.5 (DI(IO0))
/QSPI_SD1: U1.59 (QSPI_SD1), U3.2 (DO(IO1))
/QSPI_SD2: U1.58 (QSPI_SD2), U3.3 (IO2)
/QSPI_SD3: U1.55 (QSPI_SD3), U3.7 (IO3)
/QSPI_SS: R4.1, U1.60 (QSPI_SS), U3.1 (~CS)
/RUN: SW20.2, U1.26 (RUN)
/VREG_AVDD: C11.1, R1.2, U1.46 (VREG_AVDD)
/VREG_LX: L1.2, U1.48 (VREG_LX)
/XIN: C16.1, U1.21 (XIN), Y1.1
/XOUT: R8.1, U1.22 (XOUT)
/~USB_BOOT: R4.2, SW19.2
CIRCLE: SW9.1, U1.36 (GPIO24)
CROSS: SW8.1, U1.31 (GPIO19)
D+: R2.1, U4.6 (D+_to_IC)
D-: R3.1, U4.5 (D-_to_IC)
DOWN: SW3.1, U1.14 (GPIO10)
GND: C1.2, C2.2, C3.2, C4.2, C5.2, C6.2, C7.2, C8.2, C9.2, C10.2, C11.2, C12.2, C13.2, C14.2, C15.2, C16.2, C17.2, C18.2, C19.2, C20.2, C21.2, C22.2, C23.2, C24.2, C25.2, C26.2, C27.2, C28.2, C29.2, C30.2, C31.2, C32.2, C33.2, C34.2, C35.2, C36.2, C37.2, C38.2, C39.2, C40.2, C41.2, C42.2, C43.2, C44.2, D1.4 (GND), D2.4 (GND), D3.4 (GND), D4.4 (GND), D5.4 (GND), D6.4 (GND), D7.4 (GND), D8.4 (GND), D9.4 (GND), D10.4 (GND), D11.4 (GND), D12.4 (GND), D13.4 (GND), D14.4 (GND), D15.4 (GND), D16.4 (GND), D17.4 (GND), D18.4 (GND), D19.4 (GND), D20.4 (GND), D21.2 (A), OPSW1.2, OPSW2.2, OPSW3.2, OPSW4.2, OPSW5.2, OPSW6.2, R6.2, R10.2, R11.2, R15.2, R16.1, SW1.2, SW2.2, SW3.2, SW4.2, SW5.2, SW6.2, SW7.2, SW8.2, SW9.2, SW10.2, SW11.2, SW12.2, SW13.2, SW14.2, SW15.2, SW16.2, SW19.1, U1.47 (VREG_PGND), U1.61 (GND), U2.2 (GND), U3.4 (GND), U4.3 (GND), U4.4 (GND), U5.1 (GND), U6.3 (GND), U7.2 (GND), U8.2 (GND), USB1.1 (GND), USB1.12 (GND), USB1.13 (SHIELD), USB2.4 (GND), USB2.5 (Shield), Y1.2, Y1.4
HD+: R5.1, U8.1 (I/O1), U8.6 (I/O1), USB2.3 (D+)
HD-: R7.1, U8.3 (I/O2), U8.4 (I/O2), USB2.2 (D-)
L1: SW15.1, U1.43 (GPIO29_ADC3)
L2: SW11.1, U1.42 (GPIO28_ADC2)
LEFT: SW2.1, U1.13 (GPIO9)
LS: SW16.1, U1.18 (GPIO14)
unnamed: C17.1, R8.2, Y1.3
unnamed: D1.3 (DOUT), R18.1
unnamed: D2.1 (DIN), R18.2
unnamed: D2.3 (DOUT), R19.1
unnamed: D3.1 (DIN), R19.2
unnamed: D3.3 (DOUT), R20.1
unnamed: D4.1 (DIN), R20.2
unnamed: D4.3 (DOUT), R21.1
unnamed: D5.1 (DIN), R21.2
unnamed: D5.3 (DOUT), R22.1
unnamed: D6.1 (DIN), R22.2
unnamed: D6.3 (DOUT), R23.1
unnamed: D7.1 (DIN), R23.2
unnamed: D7.3 (DOUT), R24.1
unnamed: D8.1 (DIN), R24.2
unnamed: D8.3 (DOUT), R25.1
unnamed: D9.1 (DIN), R25.2
unnamed: D9.3 (DOUT), R26.1
unnamed: D10.1 (DIN), R26.2
unnamed: D10.3 (DOUT), R27.1
unnamed: D11.3 (DOUT), R28.1
unnamed: D12.1 (DIN), R28.2
unnamed: D12.3 (DOUT), R29.1
unnamed: D13.1 (DIN), R29.2
unnamed: D13.3 (DOUT), R30.1
unnamed: D14.1 (DIN), R30.2
unnamed: D14.3 (DOUT), R31.1
unnamed: D15.1 (DIN), R31.2
unnamed: D15.3 (DOUT), R32.1
unnamed: D16.1 (DIN), R32.2
unnamed: D16.3 (DOUT), R33.1
unnamed: D17.1 (DIN), R33.2
unnamed: D17.3 (DOUT), D18.1 (DIN)
unnamed: D18.3 (DOUT), D19.1 (DIN)
unnamed: D19.3 (DOUT), D20.1 (DIN)
unnamed: D21.1 (K), F1.1, USB1.2 (VBUS), USB1.11 (VBUS)
unnamed: R6.1, SW20.1
unnamed: R5.2, U1.32 (GPIO20)
unnamed: R7.2, U1.33 (GPIO21)
unnamed: R3.2, U1.51 (USB_DM)
unnamed: R2.2, U1.52 (USB_DP)
unnamed: U4.1 (D+_to_connector), USB1.6 (DP1), USB1.8 (DP2)
unnamed: U4.2 (D-_to_connector), USB1.5 (DN2), USB1.7 (DN1)
unnamed: R11.1, USB1.4 (CC1)
unnamed: R10.1, USB1.10 (CC2)
OPT1: OPSW1.1, U1.9 (GPIO6)
OPT2: OPSW2.1, U1.8 (GPIO5)
OPT3: OPSW3.1, U1.7 (GPIO4)
OPT4: OPSW4.1, U1.5 (GPIO3)
OPT5: OPSW5.1, U1.4 (GPIO2)
OPT6: OPSW6.1, U1.3 (GPIO1)
R1: SW14.1, U1.41 (GPIO27_ADC1)
R2: SW10.1, U1.40 (GPIO26_ADC0)
RGB: U1.12 (GPIO8), U6.2 (A)
RIGHT: SW4.1, U1.15 (GPIO11)
RS: SW7.1, U1.19 (GPIO15)
SCL: R12.1, U1.17 (GPIO13), U5.3 (SCL)
SDA: R13.1, U1.16 (GPIO12), U5.4 (SDA)
SQUARE: SW12.1, U1.29 (GPIO18)
TRIANGLE: SW13.1, U1.37 (GPIO25)
UP: SW1.1, U1.27 (GPIO16)
UP2: SW5.1, U1.34 (GPIO22)
UP3: SW6.1, U1.35 (GPIO23)
USB_HOST_5V: C19.1, C43.1, C44.1, U7.6 (OUT), U8.5 (VBUS), USB2.1 (VBUS)
USB_HOST_EN: R16.2, U1.10 (GPIO7), U7.3 (EN)
USB_HOST_FAULT_N: R17.2, U1.28 (GPIO17), U7.4 (FAULT_N)
USB_HOST_ILIM: R15.1, U7.5 (ILIM)

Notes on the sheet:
USB (downstream facing)
Flash
Crystal
USB (upstream facing)
OLED status display (I2C)
Power
USB2 dongle-only VBUS: 200k ILIM = 135mA nominal (115-159mA incl. 1% R); not a total USB input limit
SW1 / index 0
SW2 / index 1
SW3 / index 2
SW4 / index 3
SW5 / index 4
SW6 / index 5
SW7 / index 6
SW8 / index 7
SW9 / index 8
SW10 / index 9
SW11 / index 10
SW12 / index 11
SW13 / index 12
SW14 / index 13
SW15 / index 14
SW16 / index 15
EDGE 1 / index 16
EDGE 2 / index 17
EDGE 3 / index 18
EDGE 4 / index 19
RGB source: GPIO8. Verify 13-button off indices 5, 6, 15 in firmware.
GP2040-CE Max Brightness target: 127/255 (~50%). Firmware setting; not a current limiter.
